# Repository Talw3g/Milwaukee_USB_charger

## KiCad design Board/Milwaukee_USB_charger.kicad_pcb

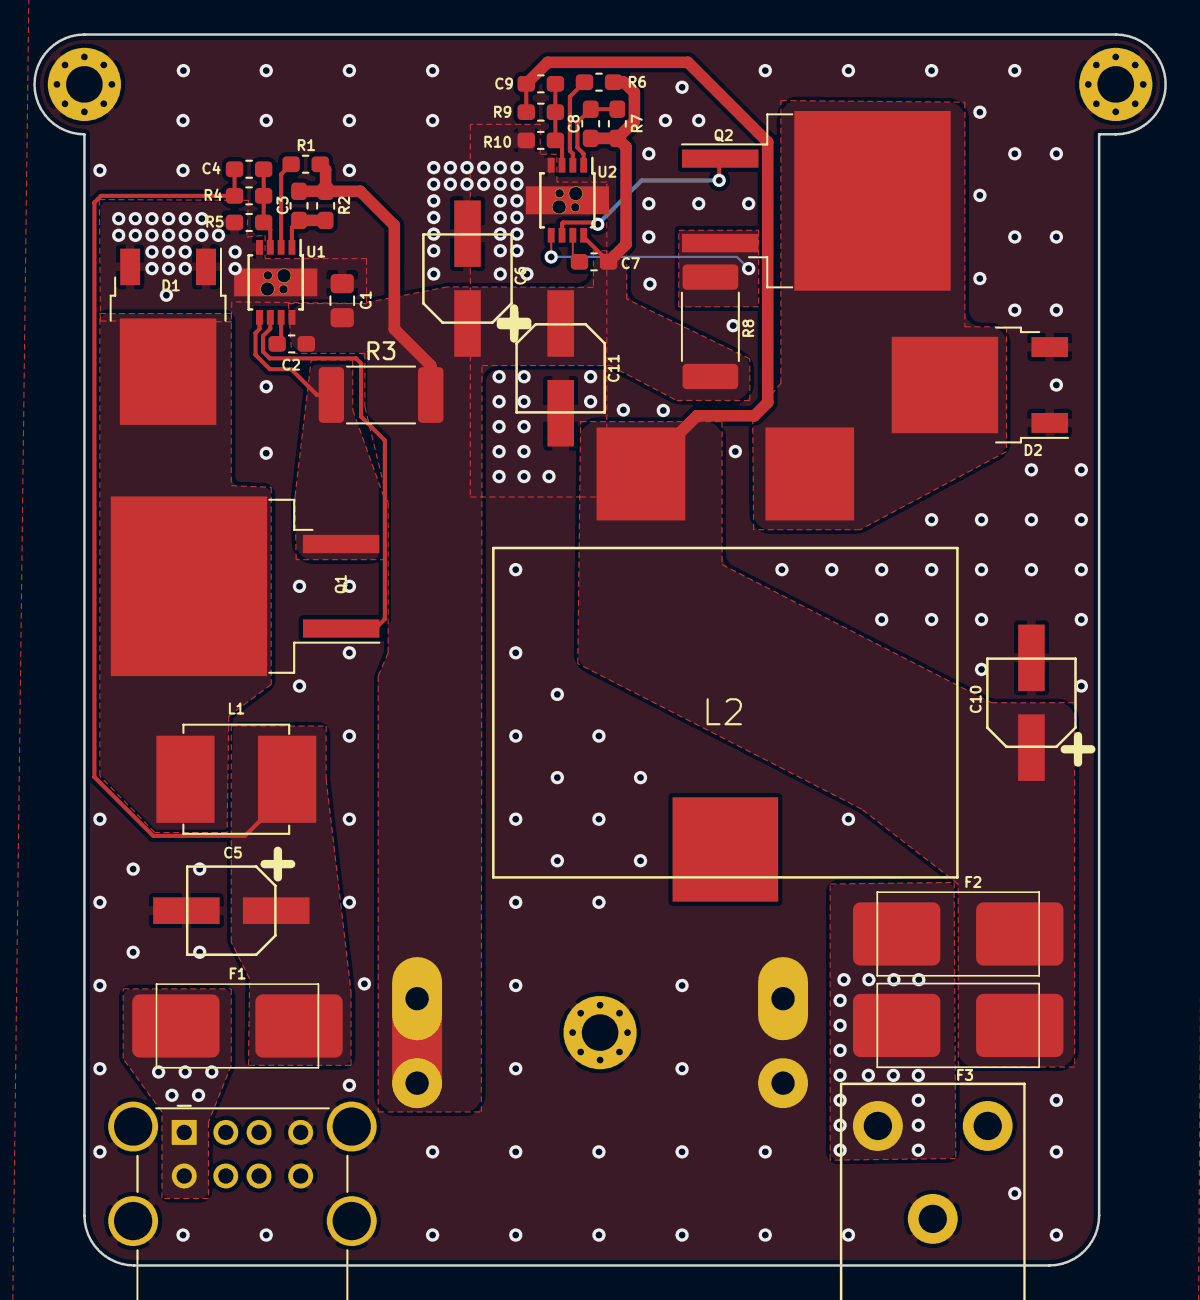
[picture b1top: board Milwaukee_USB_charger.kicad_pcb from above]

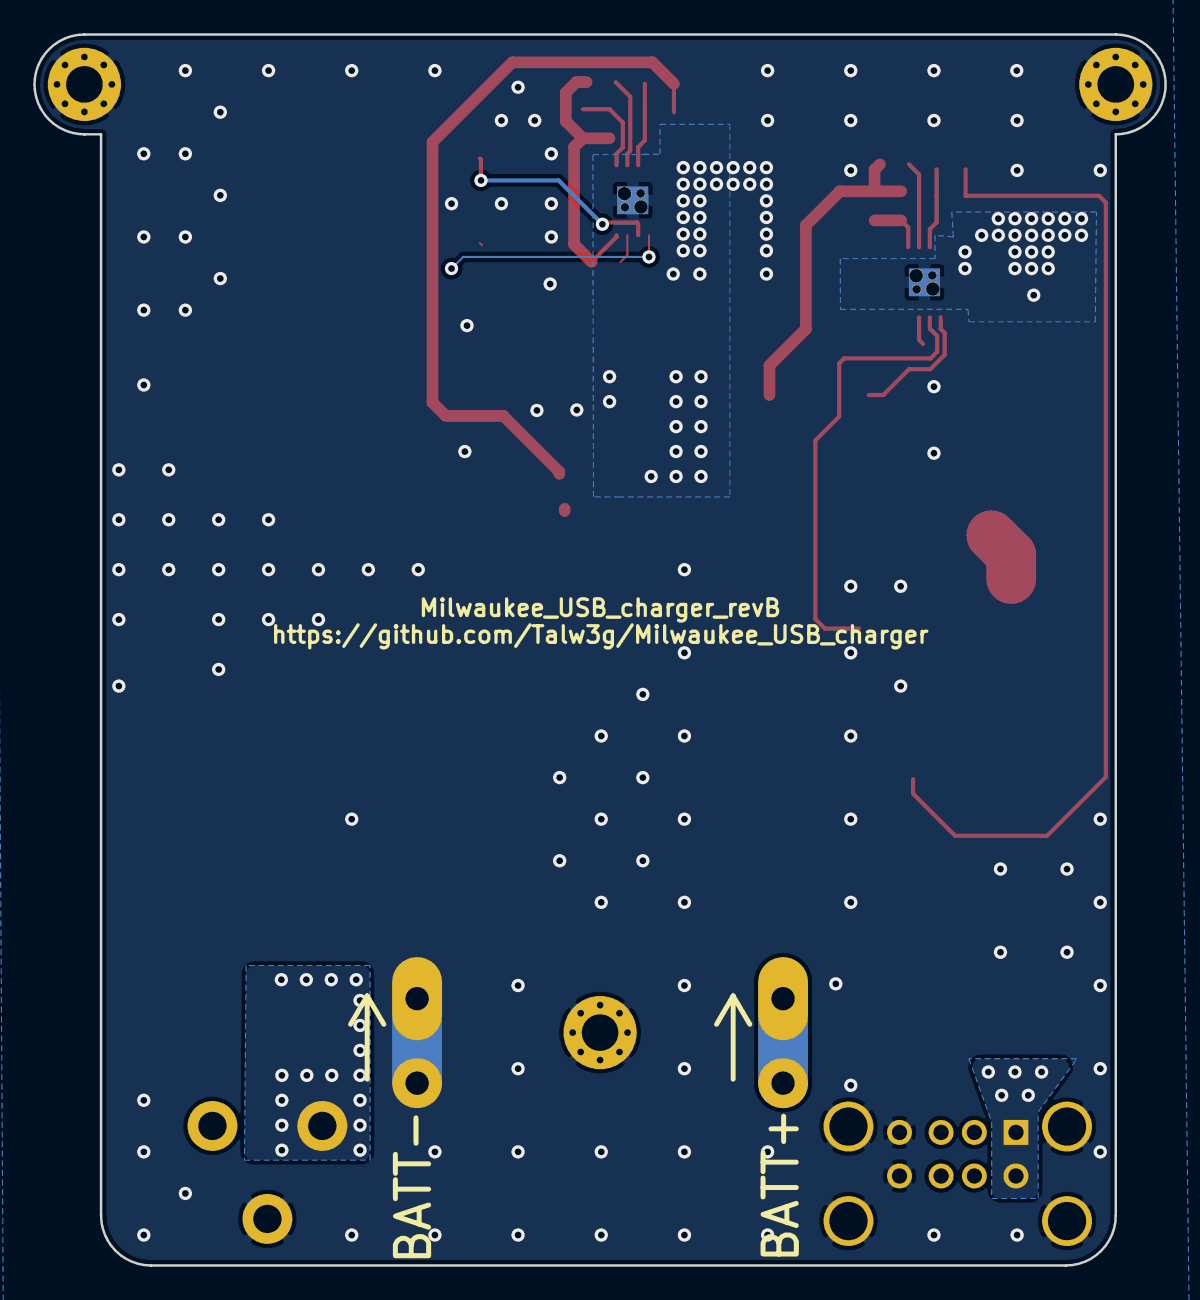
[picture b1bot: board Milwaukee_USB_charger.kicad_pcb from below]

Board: 2 copper layers, 68.0 x 74.0 mm, 39 parts (2 on the bottom side), 20 nets.

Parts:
C1: 4.7uF/25V; C_0805_2012Metric_Pad1.15x1.40mm_HandSolder
C2, C7: 1uF/25V; C_0603_1608Metric_Pad1.05x0.95mm_HandSolder
C3, C8: 1nF/50V; C_0603_1608Metric_Pad1.05x0.95mm_HandSolder
C4, C9: 10nF/50V; C_0603_1608Metric_Pad1.05x0.95mm_HandSolder
C5, C6, C10, C11: 47uF/25V; 25SVPF47M
D1, D2: D_Schottky_AKA; TO-252-2
F1: Fuse 5A; Fuse_holder_Littelfuse_154
F2, F3: Fuse 7A; Fuse_holder_Littelfuse_154
H1, H2, H3: MountingHole_Pad; MountingHole_2.2mm_M2_Pad_Via
J1: BATT+; TE_PCB-Tab_63951-1
J2: BATT-; TE_PCB-Tab_63951-1
J3: USB_A_Stacked; USB_A_Molex_67298-4090_Horizontal_Stacked
J4: Barrel_Jack_Switch; BarrelJack_712RA
L1: 8.2uH; Coilcraft_XAL6060-822MEC
L2: 10uH; Coilcraft_SER2915L-103KL
Q1, Q2: Q_PMOS_GDS; TO-263-2
R1: 44.2k; R_0603_1608Metric_Pad1.05x0.95mm_HandSolder
R2: 2.21k; R_0603_1608Metric_Pad1.05x0.95mm_HandSolder
R3, R8: 10m/2W; R_2512_6332Metric_Pad1.52x3.35mm_HandSolder
R4, R9: 10k; R_0603_1608Metric_Pad1.05x0.95mm_HandSolder
R5: 3.32k; R_0603_1608Metric_Pad1.05x0.95mm_HandSolder
R6: 383k; R_0603_1608Metric_Pad1.05x0.95mm_HandSolder
R7: 4.12k; R_0603_1608Metric_Pad1.05x0.95mm_HandSolder
R10: 1.15k; R_0603_1608Metric_Pad1.05x0.95mm_HandSolder
U1, U2: LM25085MY; LM25085MY_Handsolder

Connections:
+5V: F1.1, J3.1, J3.5
+12V: F2.1, F3.1, J4.1
BATT+: C1.1, C2.1, C3.2, C6.1, C7.1, C8.2, C11.1, J1.1, R1.1, R2.1, R3.2, R6.1, R7.1, R8.2, U1.8, U2.8
GND: C1.2, C5.2, C6.2, C10.2, C11.2, D1.1, D1.3, D2.1, D2.3, H1.1, H2.1, H3.1, J2.1, J3.4, J3.8, J3.9, J4.2, R5.1, R10.1, U1.4, U1.9, U2.4, U2.9
unnamed: C2.2, U1.7
unnamed: C3.1, R2.2, U1.1
unnamed: C4.1, C5.1, F1.2, L1.2, R4.2
unnamed: C4.2, R4.1, R5.2, U1.3
unnamed: C7.2, U2.7
unnamed: C8.1, R7.2, U2.1
unnamed: C9.2, R9.1, R10.2, U2.3
unnamed: C9.1, C10.1, F2.2, F3.2, L2.2, R9.2
unnamed: D1.2, L1.1, Q1.2
unnamed: D2.2, L2.1, Q2.2
unnamed: Q1.1, U1.6
unnamed: Q1.3, R3.1, U1.5
unnamed: Q2.1, U2.6
unnamed: Q2.3, R8.1, U2.5
unnamed: R1.2, U1.2
unnamed: R6.2, U2.2

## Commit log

2018-12-19 First commit.
2019-01-27 Routing done.
2019-02-03 Routing done, waiting for mechanical integration.
2019-02-07 Changed current measuring res, updated routing.
2019-02-16 REPLACE PREVIOUS COMMIT.
2019-04-02 Added one fuse and changed 10mOhm res to withstand 12A+
2019-04-07 CAD done.
2019-04-07 Updated silkscreen.
2019-05-04 Used to 2W res instead of one 0.5W + one 2W
2019-05-15 Added gerber files.
2019-06-23 /!\ Corrected schottky diode symbol !
2019-06-29 Gerber files generated : revB
2019-09-07 Updated board 3D to revB
2019-09-08 Removed expansion insert from assy.
2019-10-05 Added manufcaturing files for casing (revA).
